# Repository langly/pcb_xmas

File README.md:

# PCB_XMAS

A small little PCB for generating a blinking xmas tree using 555 timer, and shift registers. 

For use in kicad

For a demo, see https://twitter.com/mrLangly/status/1589393416126746624

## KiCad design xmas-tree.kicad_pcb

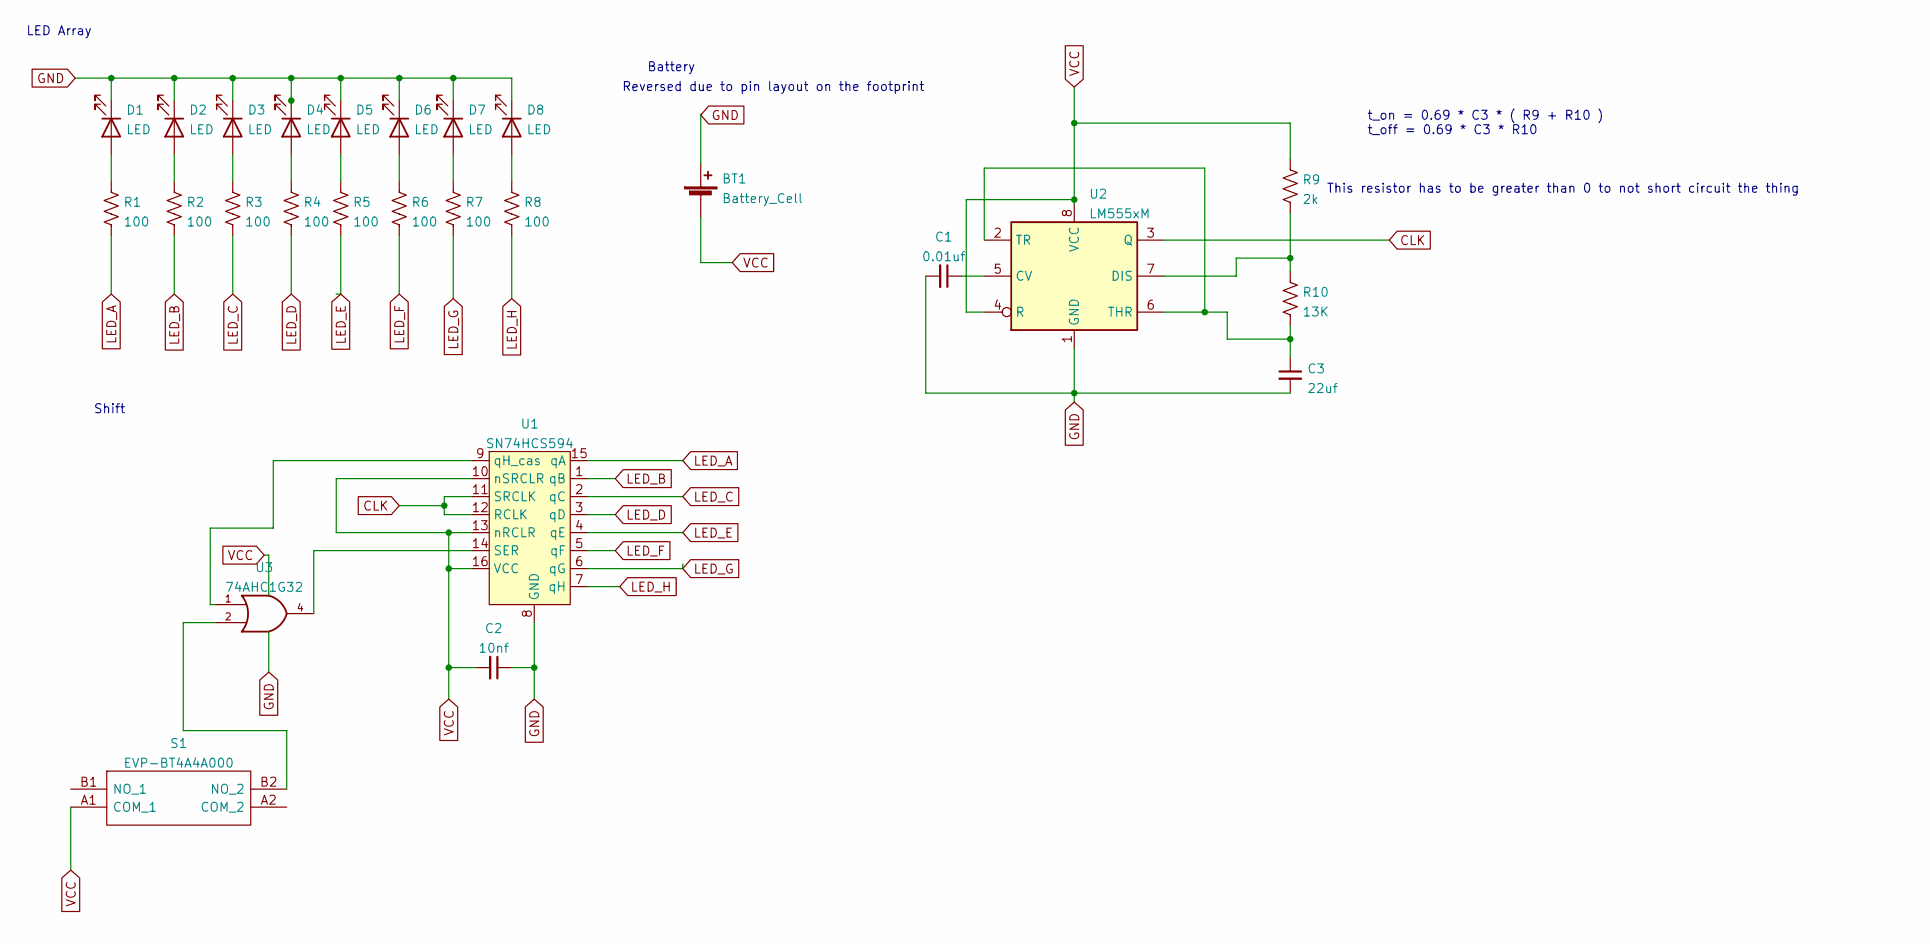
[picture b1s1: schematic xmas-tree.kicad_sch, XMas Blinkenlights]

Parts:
BT1: Battery_Cell; 101
C1: 0.01uf; C_0805_2012Metric_Pad1.18x1.45mm_HandSolder
C2: 10nf; C_0805_2012Metric_Pad1.18x1.45mm_HandSolder
C3: 22uf; C_0805_2012Metric_Pad1.18x1.45mm_HandSolder
D1, D2, D3, D4, D5, D6, D7, D8: LED; LED_D5.0mm_Clear
R1, R2, R3, R4, R5, R6, R7, R8: 100; R_0805_2012Metric_Pad1.20x1.40mm_HandSolder
R9: 2k; R_0805_2012Metric_Pad1.20x1.40mm_HandSolder
R10: 13K; R_0805_2012Metric_Pad1.20x1.40mm_HandSolder
S1: EVP-BT4A4A000; EVPBT4A4A000; Mouser Part Number 769-EVP-BT4A4A000
U1: SN74HCS594; SOIC-16_3.9x9.9mm_P1.27mm
U2: LM555xM; SOIC-8_3.9x4.9mm_P1.27mm
U3: 74AHC1G32; SOT-353_SC-70-5_Handsoldering

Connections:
CLK: U1.11 (SRCLK), U1.12 (RCLK), U2.3 (Q)
GND: BT1.1 (+), C1.2, C2.1, C3.2, D1.1 (K), D2.1 (K), D3.1 (K), D4.1 (K), D5.1 (K), D6.1 (K), D7.1 (K), D8.1 (K), U1.8 (GND), U2.1 (GND), U3.3 (GND)
LED_A: R1.2, U1.15 (qA)
LED_B: R2.2, U1.1 (qB)
LED_C: R3.2, U1.2 (qC)
LED_D: R4.2, U1.3 (qD)
LED_E: R5.2, U1.4 (qE)
LED_F: R6.2, U1.5 (qF)
LED_G: R7.2, U1.6 (qG)
LED_H: R8.2, U1.7 (qH)
unnamed: C1.1, U2.5 (CV)
unnamed: C3.1, R10.2, U2.2 (TR), U2.6 (THR)
unnamed: D1.2 (A), R1.1
unnamed: D2.2 (A), R2.1
unnamed: D3.2 (A), R3.1
unnamed: D4.2 (A), R4.1
unnamed: D5.2 (A), R5.1
unnamed: D6.2 (A), R6.1
unnamed: D7.2 (A), R7.1
unnamed: D8.2 (A), R8.1
unnamed: R9.2, R10.1, U2.7 (DIS)
unnamed: S1.B2 (NO_2), U3.2
unnamed: U1.9 (qH_cas), U3.1
unnamed: U1.14 (SER), U3.4
VCC: BT1.2 (-), C2.2, R9.1, S1.A1 (COM_1), U1.10 (nSRCLR), U1.13 (nRCLR), U1.16 (VCC), U2.4 (R), U2.8 (VCC), U3.5 (VCC)

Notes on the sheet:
t_on = 0.69 * C3 * ( R9 + R10 ) t_off = 0.69 * C3 * R10
Reversed due to pin layout on the footprint
LED Array
Shift
Battery
This resistor has to be greater than 0 to not short circuit the thing

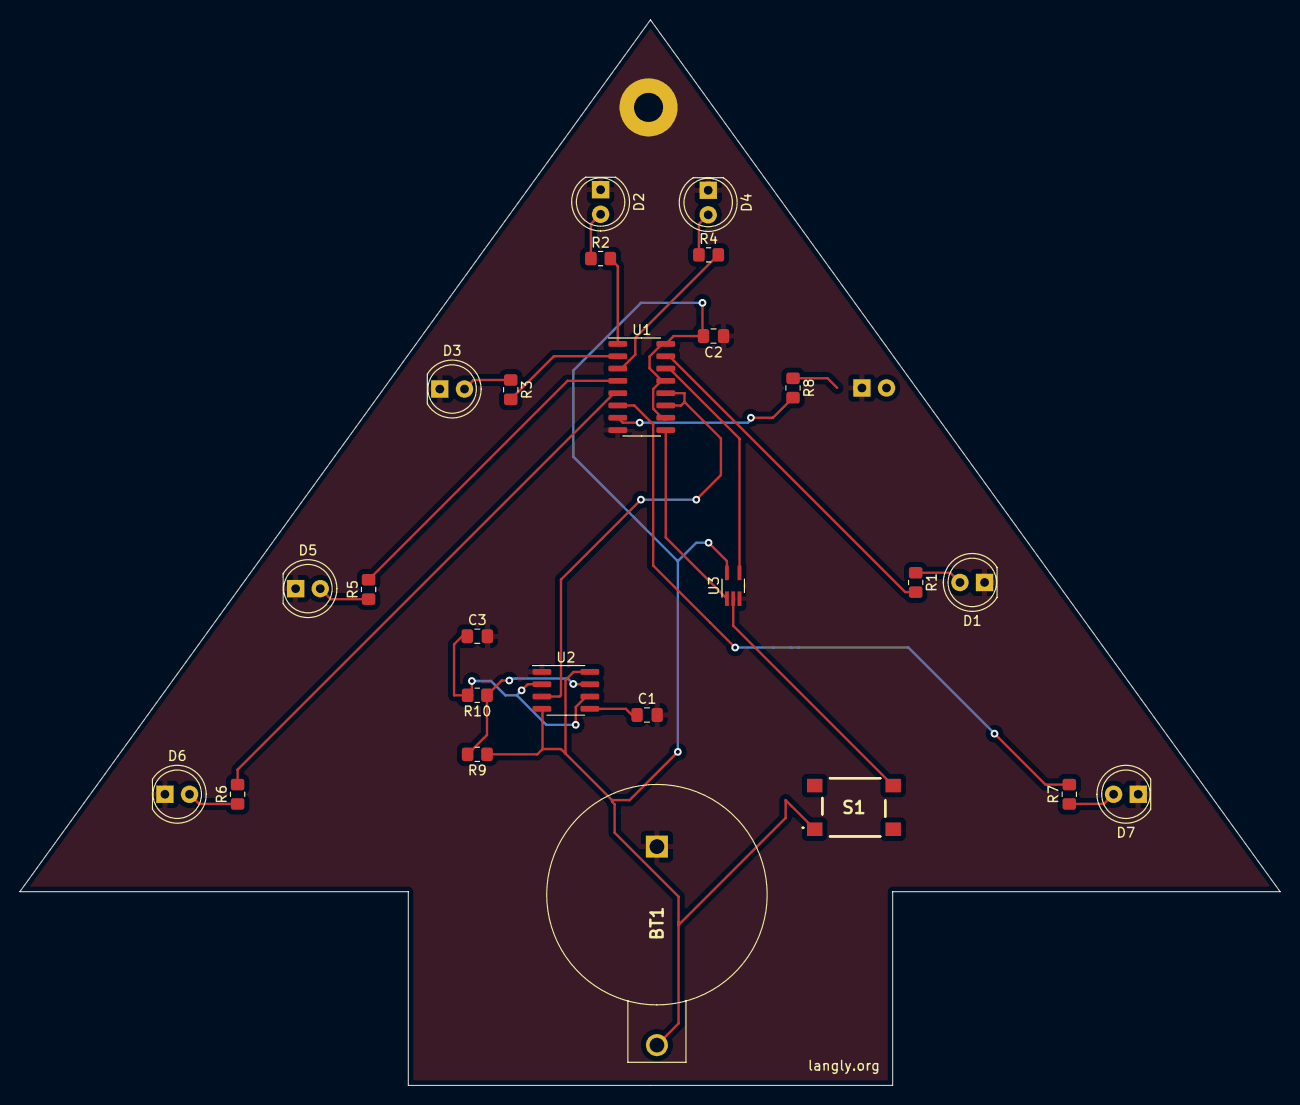
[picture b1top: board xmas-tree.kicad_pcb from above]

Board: 2 copper layers, 130.1 x 110.0 mm, 26 parts (1 on the bottom side), 25 nets.

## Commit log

2022-10-30 Added version 0.1
2022-11-07 Updated the values in the BoM
2022-11-08 Fixed the problem of the battery holder being the wrong way
